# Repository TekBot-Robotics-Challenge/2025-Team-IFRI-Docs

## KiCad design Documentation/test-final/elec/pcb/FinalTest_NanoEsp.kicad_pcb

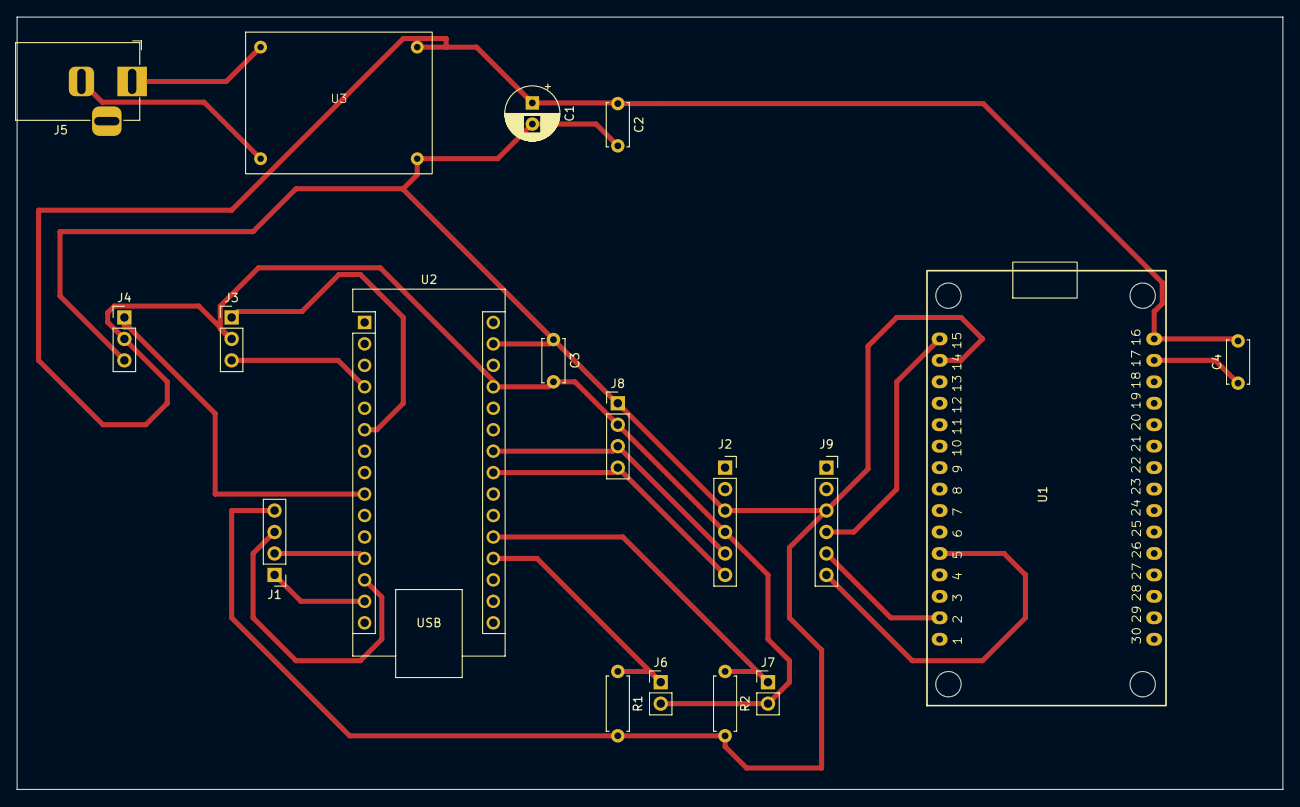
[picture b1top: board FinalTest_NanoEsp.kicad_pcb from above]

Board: 2 copper layers, 149.9 x 91.4 mm, 18 parts (0 on the bottom side), 16 nets.

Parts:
C1: 100µ; CP_Radial_D6.3mm_P2.50mm
C2, C3, C4: 100n; C_Disc_D5.0mm_W2.5mm_P5.00mm
J1: L298N; PinHeader_1x04_P2.54mm_Vertical
J2: BSS138H; PinSocket_1x06_P2.54mm_Vertical
J3: Laser_KY-008_2; PinHeader_1x03_P2.54mm_Vertical
J4: Laser_KY-008_1; PinHeader_1x03_P2.54mm_Vertical
J5: Jack-DC; BarrelJack_Horizontal
J6: Photo_R1; PinHeader_1x02_P2.54mm_Vertical
J7: Photo_R2; PinHeader_1x02_P2.54mm_Vertical
J8: Color_GY_33; PinHeader_1x04_P2.54mm_Vertical
J9: BSS138L; PinSocket_1x06_P2.54mm_Vertical
R1, R2: 10k; R_Axial_DIN0207_L6.3mm_D2.5mm_P7.62mm_Horizontal
U1: ESP32_30pin
U2: Arduino_Nano
U3: Buck_DC_DC

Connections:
/5V: C1.1, C2.1, C3.2, C4.2, J2.4, J3.2, J4.2, J6.2, J7.2, J8.2, U1.15 (EN), U2.27 (+5V), U3.1 (OUT+)
/ENA: J1.1, U2.14 (MOSI)
/GND: C1.2, C2.2, C3.1, C4.1, J1.4, J2.3, J3.3, J4.3, J8.1, J9.3, R1.2, R2.2, U1.14 (GPIO36), U2.4 (GND), U2.29 (GND), U3.2 (OUT-)
/HV1: J2.6, J8.4, U2.23 (SDA/A4)
/HV2: J2.5, J8.3, U2.24 (SCL/A5)
/IN1: J1.2, U2.12 (D9)
/IN2: J1.3, U2.13 (D10)
/LV: J9.4, U1.15 (EN)
/LV1: J9.6, U1.5 (GPIO14)
/LV2: J9.5, U1.2 (GND)
/S1: J4.1, U2.9 (D6)
/S2: J3.1, U2.6 (D3)
unnamed: J6.1, R1.1, U2.19 (A0)
unnamed: J7.1, R2.1, U2.20 (A1)
unnamed: J5.1, U3.4 (IN+)
unnamed: J5.2, U3.3 (IN-)

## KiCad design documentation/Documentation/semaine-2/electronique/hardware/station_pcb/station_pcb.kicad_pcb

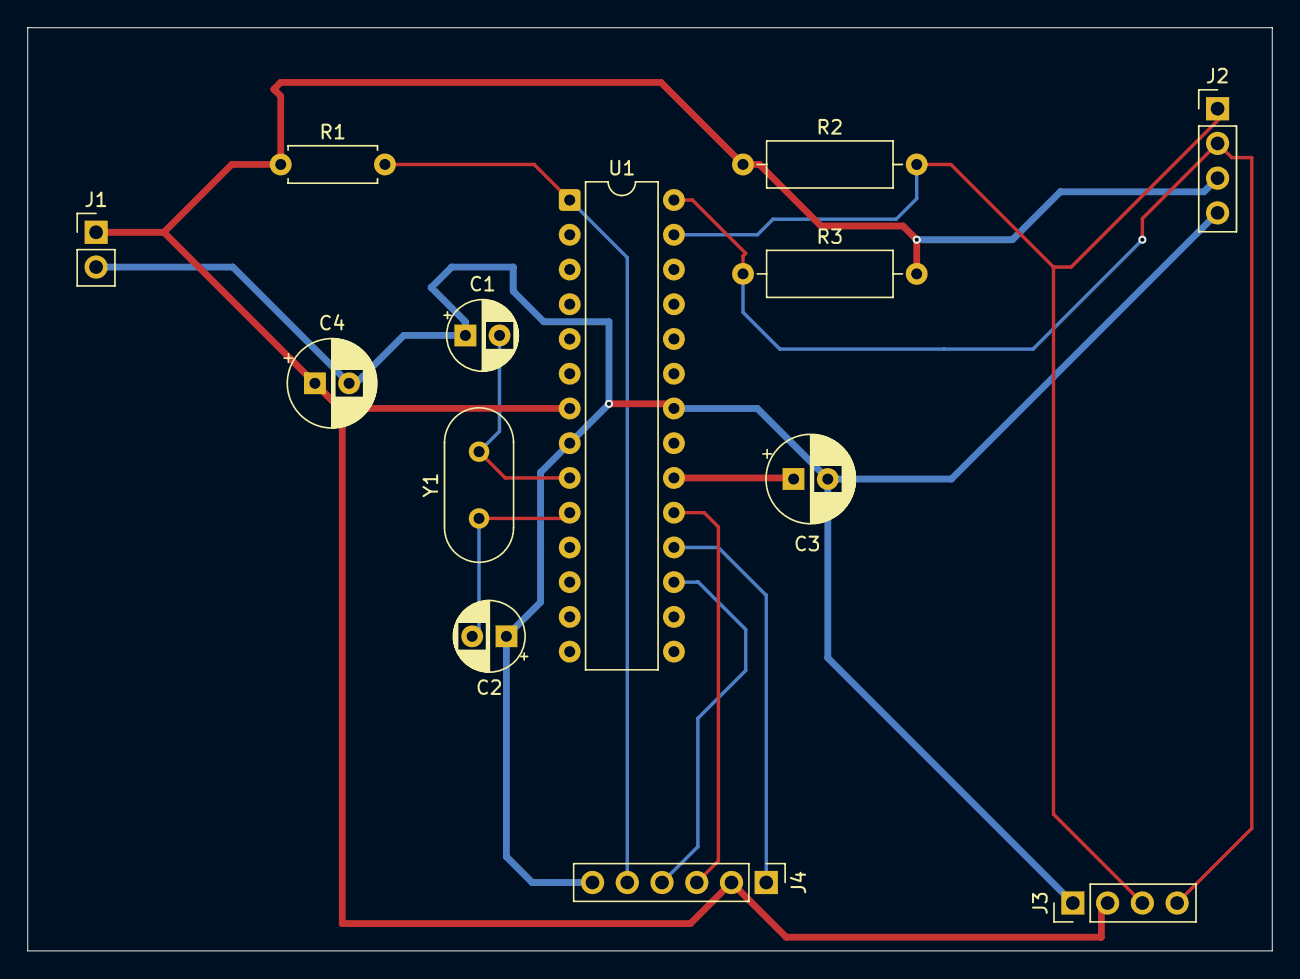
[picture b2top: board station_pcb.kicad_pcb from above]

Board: 2 copper layers, 91.0 x 67.5 mm, 13 parts (0 on the bottom side), 11 nets.

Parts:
C1, C2: 22p; CP_Radial_D5.0mm_P2.50mm
C3, C4: 100n; CP_Radial_D6.3mm_P2.50mm
J1: Conn_Alimentation; PinHeader_1x02_P2.54mm_Vertical
J2: Bus_I2C_Commun; PinHeader_1x04_P2.54mm_Vertical
J3: LCD_I2C; PinHeader_1x04_P2.54mm_Vertical
J4: Programmateur_ISP; PinHeader_1x06_P2.54mm_Vertical
R1: 10k; R_Axial_DIN0207_L6.3mm_D2.5mm_P7.62mm_Horizontal
R2, R3: 4k7; R_Axial_DIN0309_L9.0mm_D3.2mm_P12.70mm_Horizontal
U1: ATmega328P-P; DIP-28_W7.62mm
Y1: Crystal; Crystal_HC49-U_Vertical

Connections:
/1 MISO: J4.1, U1.18 (PB4)
/3 SCK: J4.3, U1.19 (PB5)
/4 MOSI: J4.4, U1.17 (PB3)
/5 RST: J4.5, R1.2, U1.1 (~RESET/PC6)
/5V: C4.1, J1.1, J2.3, J3.2, J4.2, R1.1, R2.1, R3.2, U1.7 (VCC)
/GND: C1.1, C2.1, C3.2, C4.2, J1.2, J2.4, J3.1, J4.6, U1.8 (GND), U1.22 (GND)
/SCL: J2.2, J3.4, R3.1, U1.28 (PC5)
/SDA: J2.1, J3.3, R2.2, U1.27 (PC4)
unnamed: C3.1, U1.20 (AVCC)
unnamed: C1.2, U1.9 (XTAL1/PB6), Y1.2
unnamed: C2.2, U1.10 (XTAL2/PB7), Y1.1

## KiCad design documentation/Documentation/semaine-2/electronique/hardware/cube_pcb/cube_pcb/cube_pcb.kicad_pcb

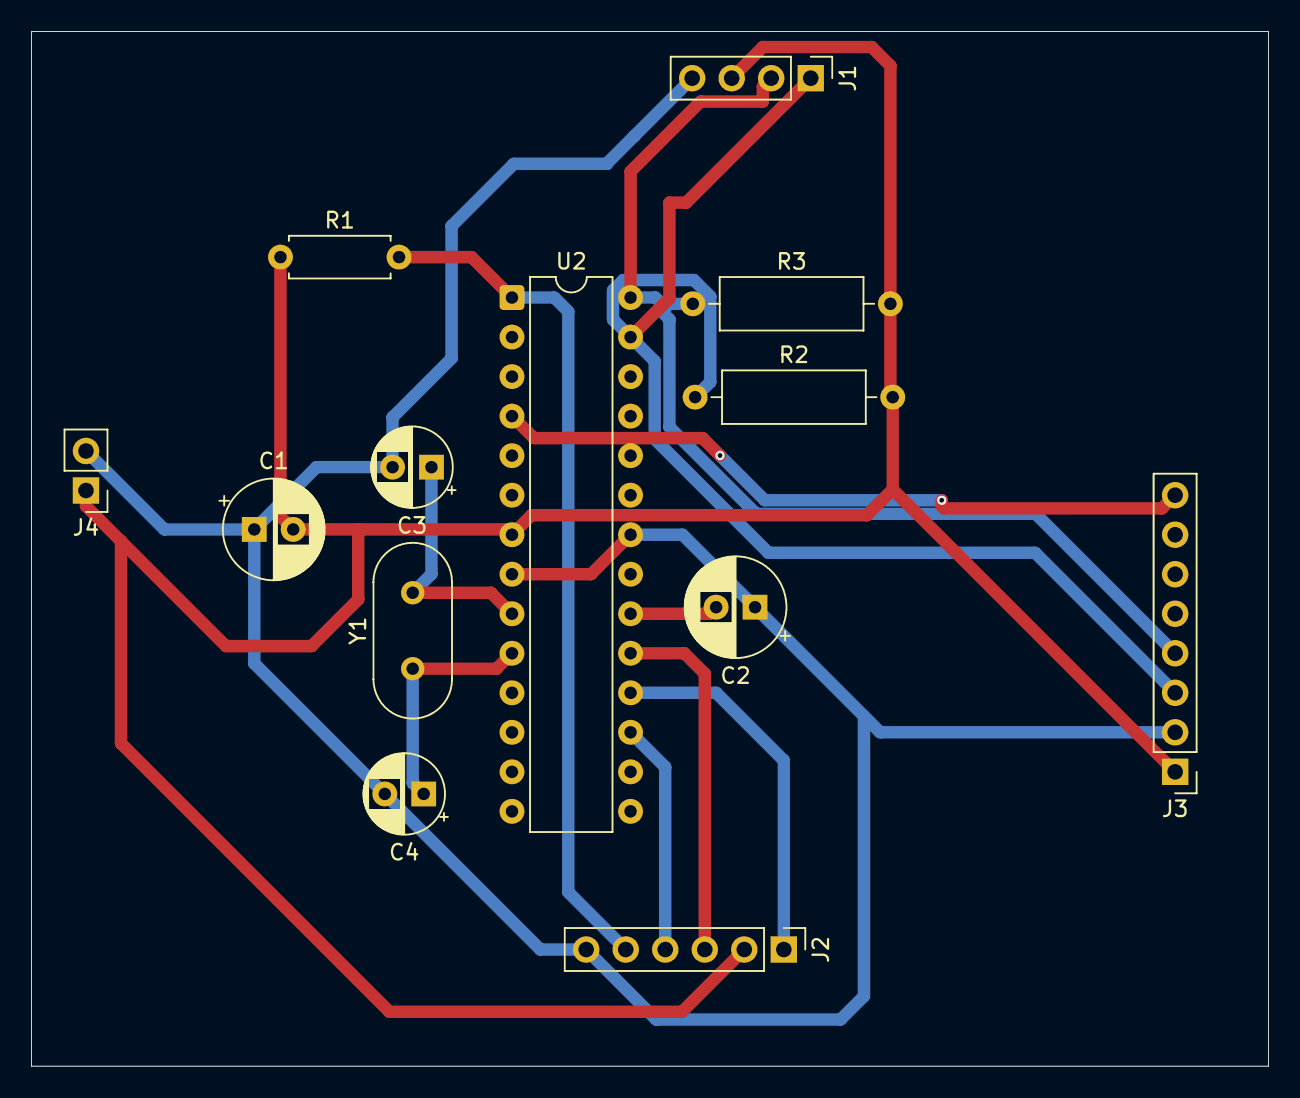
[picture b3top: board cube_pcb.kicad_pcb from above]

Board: 2 copper layers, 79.5 x 66.5 mm, 13 parts (0 on the bottom side), 12 nets.

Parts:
C1, C2: 100n; CP_Radial_D6.3mm_P2.50mm
C3, C4: 22p; CP_Radial_D5.0mm_P2.50mm
J1: Bus_I2C_Commun; PinHeader_1x04_P2.54mm_Vertical
J2: Programmateur_ISP; PinHeader_1x06_P2.54mm_Vertical
J3: MPU-6050; PinHeader_1x08_P2.54mm_Vertical
J4: Conn_Alimentation; PinHeader_1x02_P2.54mm_Vertical
R1: 10k; R_Axial_DIN0207_L6.3mm_D2.5mm_P7.62mm_Horizontal
R2, R3: 4.7k; R_Axial_DIN0309_L9.0mm_D3.2mm_P12.70mm_Horizontal
U2: ATmega328P-P; DIP-28_W7.62mm
Y1: Crystal; Crystal_HC49-U_Vertical

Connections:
/1 MISO: J2.1, U2.18 (PB4)
/3 SCK: J2.3, U2.19 (PB5)
/4 MOSI: J2.4, U2.17 (PB3)
/5 RST: J2.5, R1.2, U2.1 (~RESET/PC6)
/5V: C1.2, J1.3, J2.2, J3.1, J4.1, R1.1, R2.2, R3.2, U2.7 (VCC)
/GND: C1.1, C2.1, C3.2, C4.2, J1.4, J2.6, J3.2, J4.2, U2.8 (GND), U2.22 (GND)
/INT0: J3.8, U2.4 (PD2)
/SCL: J1.2, J3.4, R3.1, U2.28 (PC5)
/SDA: J1.1, J3.3, R2.1, U2.27 (PC4)
unnamed: C2.2, U2.20 (AVCC)
unnamed: C3.1, U2.9 (XTAL1/PB6), Y1.2
unnamed: C4.1, U2.10 (XTAL2/PB7), Y1.1

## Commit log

2025-06-12 Ajout des nouveaux fichiers
2025-06-12 docs: ajout de la documentation électronique avec images et mise à jour de la structure
2025-06-12 Remplacement complet du contenu par la nouvelle version
2025-06-12 Deploy documentation to GitHub Pages
2025-06-15 [ADD]: Pieces files links in the documentation
2025-06-16 Amélioration du design et correction des bugs
2025-06-16 Correction des fichiers dupliqués et des erreurs
2025-06-17 Refonte complète du design avec thème sombre/clair et structure responsive
2025-06-17 Version finale appliquée depuis le stash
2025-06-17 Refonte du design avec thème Discord-like
2025-06-18 Reconstruction du site après problèmes
2025-06-18 Documentation du projet IFRI 2025
2025-06-19 Restructuration de l'architecture
2025-06-19 [ADD]: Team meca Week-2 documentation
2025-06-19 [ADD]: test mecanique
2025-06-19 [ADD]: test 2 Documentation
2025-06-22 corection des liens de la sidebare
2025-06-22 corection des liens du stryl
2025-06-24 corections des bugs
2025-07-11 test final
2025-07-12 third
2025-07-26 mise à jour de la documentation mecanique
2025-07-26 save
2025-07-28 vidéos
2025-08-10 push of a new branch phoris
2025-08-10 update phoris's branch to include all repertory
2025-08-10 re-update
2025-08-12 update the meca documentation for test final in fr
2025-08-12 suppress the .vscode repertory
2025-08-12 update in html all of the mecanique documentation in fr
2025-10-28 clean
2025-10-28 new docs
2025-11-26 ajout des logos
2025-12-01 corection des logos dans le footer et ajout du 10 eme membre de l'équipe
2026-01-27 doc final begning
